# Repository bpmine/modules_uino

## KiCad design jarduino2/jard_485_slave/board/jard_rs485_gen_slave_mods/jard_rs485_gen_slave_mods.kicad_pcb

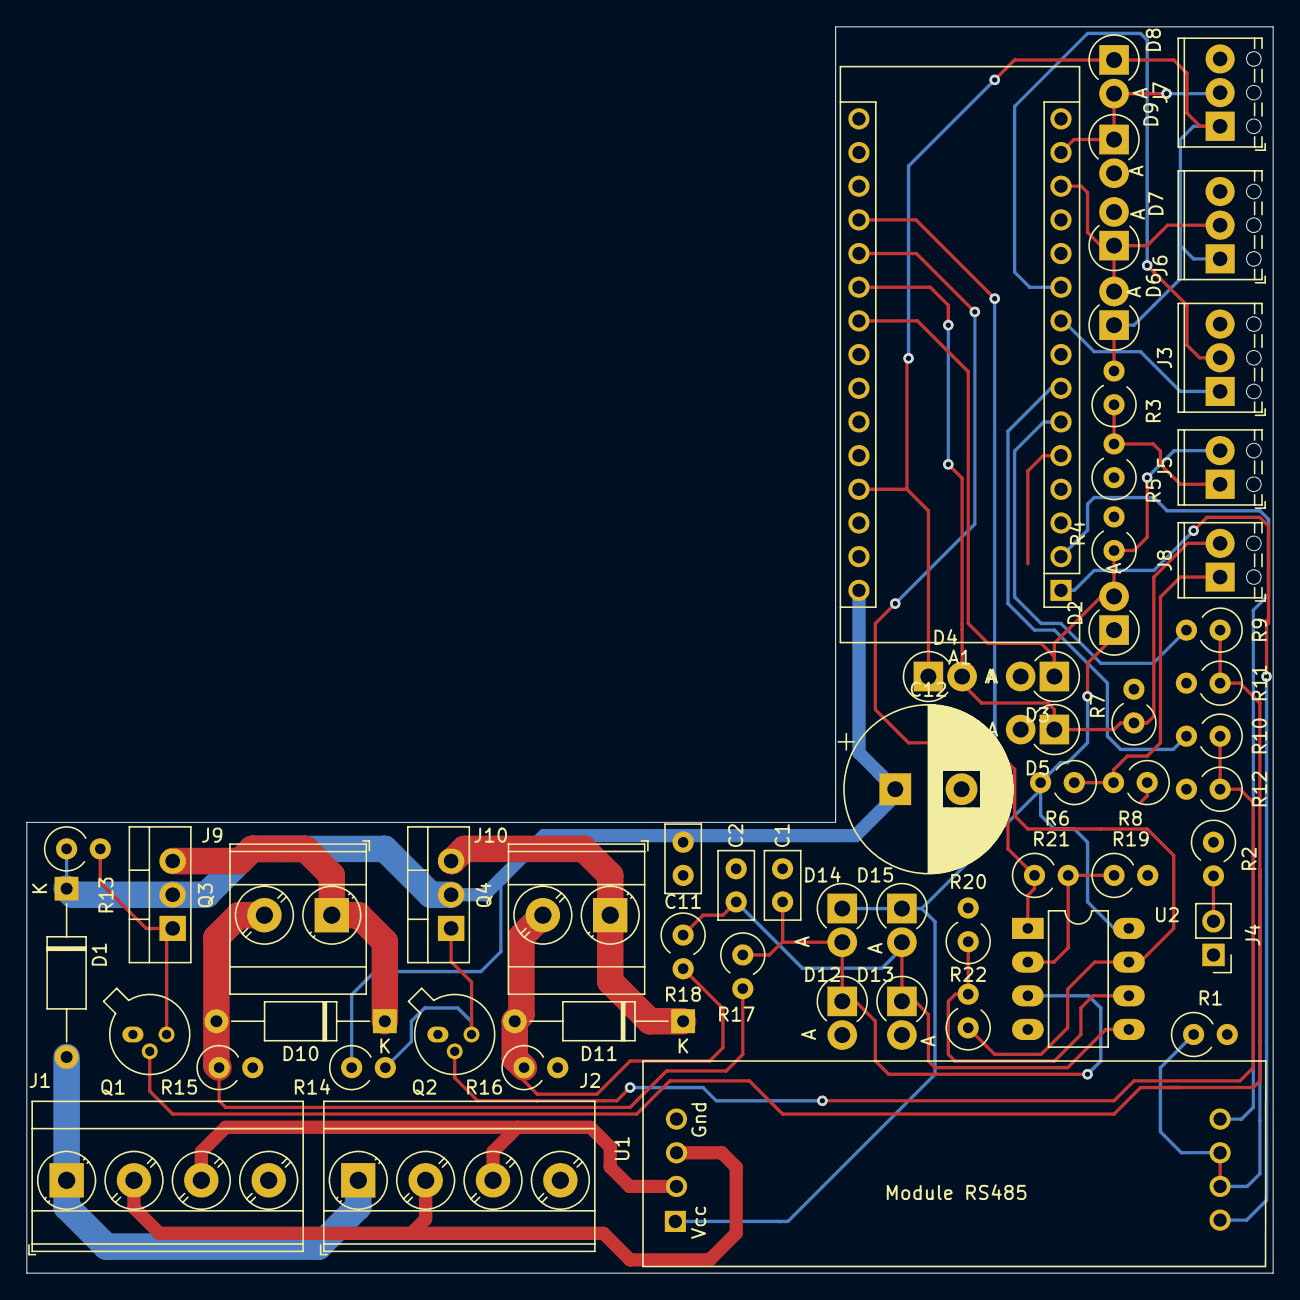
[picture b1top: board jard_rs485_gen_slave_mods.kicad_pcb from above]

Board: 2 copper layers, 94.0 x 94.0 mm, 58 parts (0 on the bottom side), 35 nets.

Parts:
A1: Arduino_Nano_v2.x; BPC_Arduino_Nano
C1, C2: C; C_Disc_D5.0mm_W2.5mm_P2.50mm
C11: 10nF; C_Disc_D5.0mm_W2.5mm_P2.50mm
C12: 20µF; CP_Radial_D12.5mm_P5.00mm
D1, D10, D11: D; D_A-405_P12.70mm_Horizontal
D2, D3, D4, D5, D6, D7, D8, D9, D12, D13, D14, D15: D_Schottky; D_DO-15_P2.54mm_Vertical_AnodeUp
J1: NETWORK IN; TerminalBlock_Phoenix_MKDS-3-4-5.08_1x04_P5.08mm_Horizontal
J2: NETWORK OUT; TerminalBlock_Phoenix_MKDS-3-4-5.08_1x04_P5.08mm_Horizontal
J3, J6, J7: Conn_01x03; TerminalBlock_Phoenix_MPT-0,5-3-2.54_1x03_P2.54mm_Horizontal
J4: LED; PinHeader_1x02_P2.54mm_Vertical
J5, J8: Conn_01x02; TerminalBlock_Phoenix_MPT-0,5-2-2.54_1x02_P2.54mm_Horizontal
J9, J10: Conn_01x02; TerminalBlock_Phoenix_MKDS-3-2-5.08_1x02_P5.08mm_Horizontal
Q1, Q2: 2N2222A; TO-18-3
Q3, Q4: bpc_mos_p03p4; TO-220-3_Vertical
R1, R11, R12, R13, R14: 100k; R_Axial_DIN0309_L9.0mm_D3.2mm_P2.54mm_Vertical
R2: 150; R_Axial_DIN0309_L9.0mm_D3.2mm_P2.54mm_Vertical
R3, R5, R6, R8: 0; R_Axial_DIN0309_L9.0mm_D3.2mm_P2.54mm_Vertical
R4, R7: 250; R_Axial_DIN0309_L9.0mm_D3.2mm_P2.54mm_Vertical
R9, R10: 50; R_Axial_DIN0309_L9.0mm_D3.2mm_P2.54mm_Vertical
R15, R16: 30m; R_Axial_DIN0309_L9.0mm_D3.2mm_P2.54mm_Vertical
R17, R18, R19, R20, R21, R22: R; R_Axial_DIN0309_L9.0mm_D3.2mm_P2.54mm_Vertical
U1: BPC_Mod485
U2: MCP6002-xP; DIP-8_W7.62mm_LongPads

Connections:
CMD_P1: A1.6, R9.2
CMD_P2: A1.7, R10.2
GND: A1.4, A1.29, C1.2, C2.2, C11.2, C12.2, D3.2, D5.2, D7.2, D9.2, D12.2, D13.2, J1.4, J2.4, J3.3, J4.1, J6.3, J7.3, Q1.1, Q2.1, R1.2, R4.2, R7.2, R11.2, R12.2, R15.2, R16.2, R19.2, R20.2, U1.4, U2.4
IN_1: A1.9, J3.1
IN_2: A1.10, J3.2
IN_PULSE_1: A1.13, D6.2, D7.1, J6.2
IN_PULSE_2: A1.14, D8.2, D9.1, J7.2
MESI_1: A1.19, R21.1, U2.1
MESI_2: A1.20, R22.1, U2.7
MESI_3: A1.21, D4.2, D5.1, J8.2, R7.1
MESI_4: A1.22, D2.2, D3.1, J5.2, R4.1
unnamed: A1.8, R2.1
unnamed: C1.1, D12.1, D14.2, R17.1, U2.3
unnamed: C2.1, D13.1, D15.2, R18.1, U2.5
unnamed: D1.2, J1.1, J2.1
unnamed: D10.1, J9.1, Q3.3
unnamed: D10.2, J9.2, R15.1, R17.2
unnamed: D11.1, J10.1, Q4.3
unnamed: D11.2, J10.2, R16.1, R18.2
unnamed: J1.2, J2.2, U1.3
unnamed: J1.3, J2.3, U1.2
unnamed: J4.2, R2.2
unnamed: J5.1, R3.1, R5.2
unnamed: J8.1, R6.1, R8.2
unnamed: Q1.2, R9.1, R11.1
unnamed: Q1.3, Q3.1, R13.2
unnamed: Q2.2, R10.1, R12.1
unnamed: Q2.3, Q4.1, R14.2
unnamed: R19.1, R21.2, U2.2
unnamed: R20.1, R22.2, U2.6
POW_MOS: A1.30, C11.1, C12.1, D1.1, Q3.2, Q4.2, R5.1, R8.1, R13.1, R14.1
RX: A1.2, U1.8
TX: A1.1, U1.5
TXEN: A1.5, R1.1, U1.6, U1.7
Vcc: A1.27, D2.1, D4.1, D6.1, D8.1, D14.1, D15.1, J6.1, J7.1, R3.2, R6.2, U1.1, U2.8

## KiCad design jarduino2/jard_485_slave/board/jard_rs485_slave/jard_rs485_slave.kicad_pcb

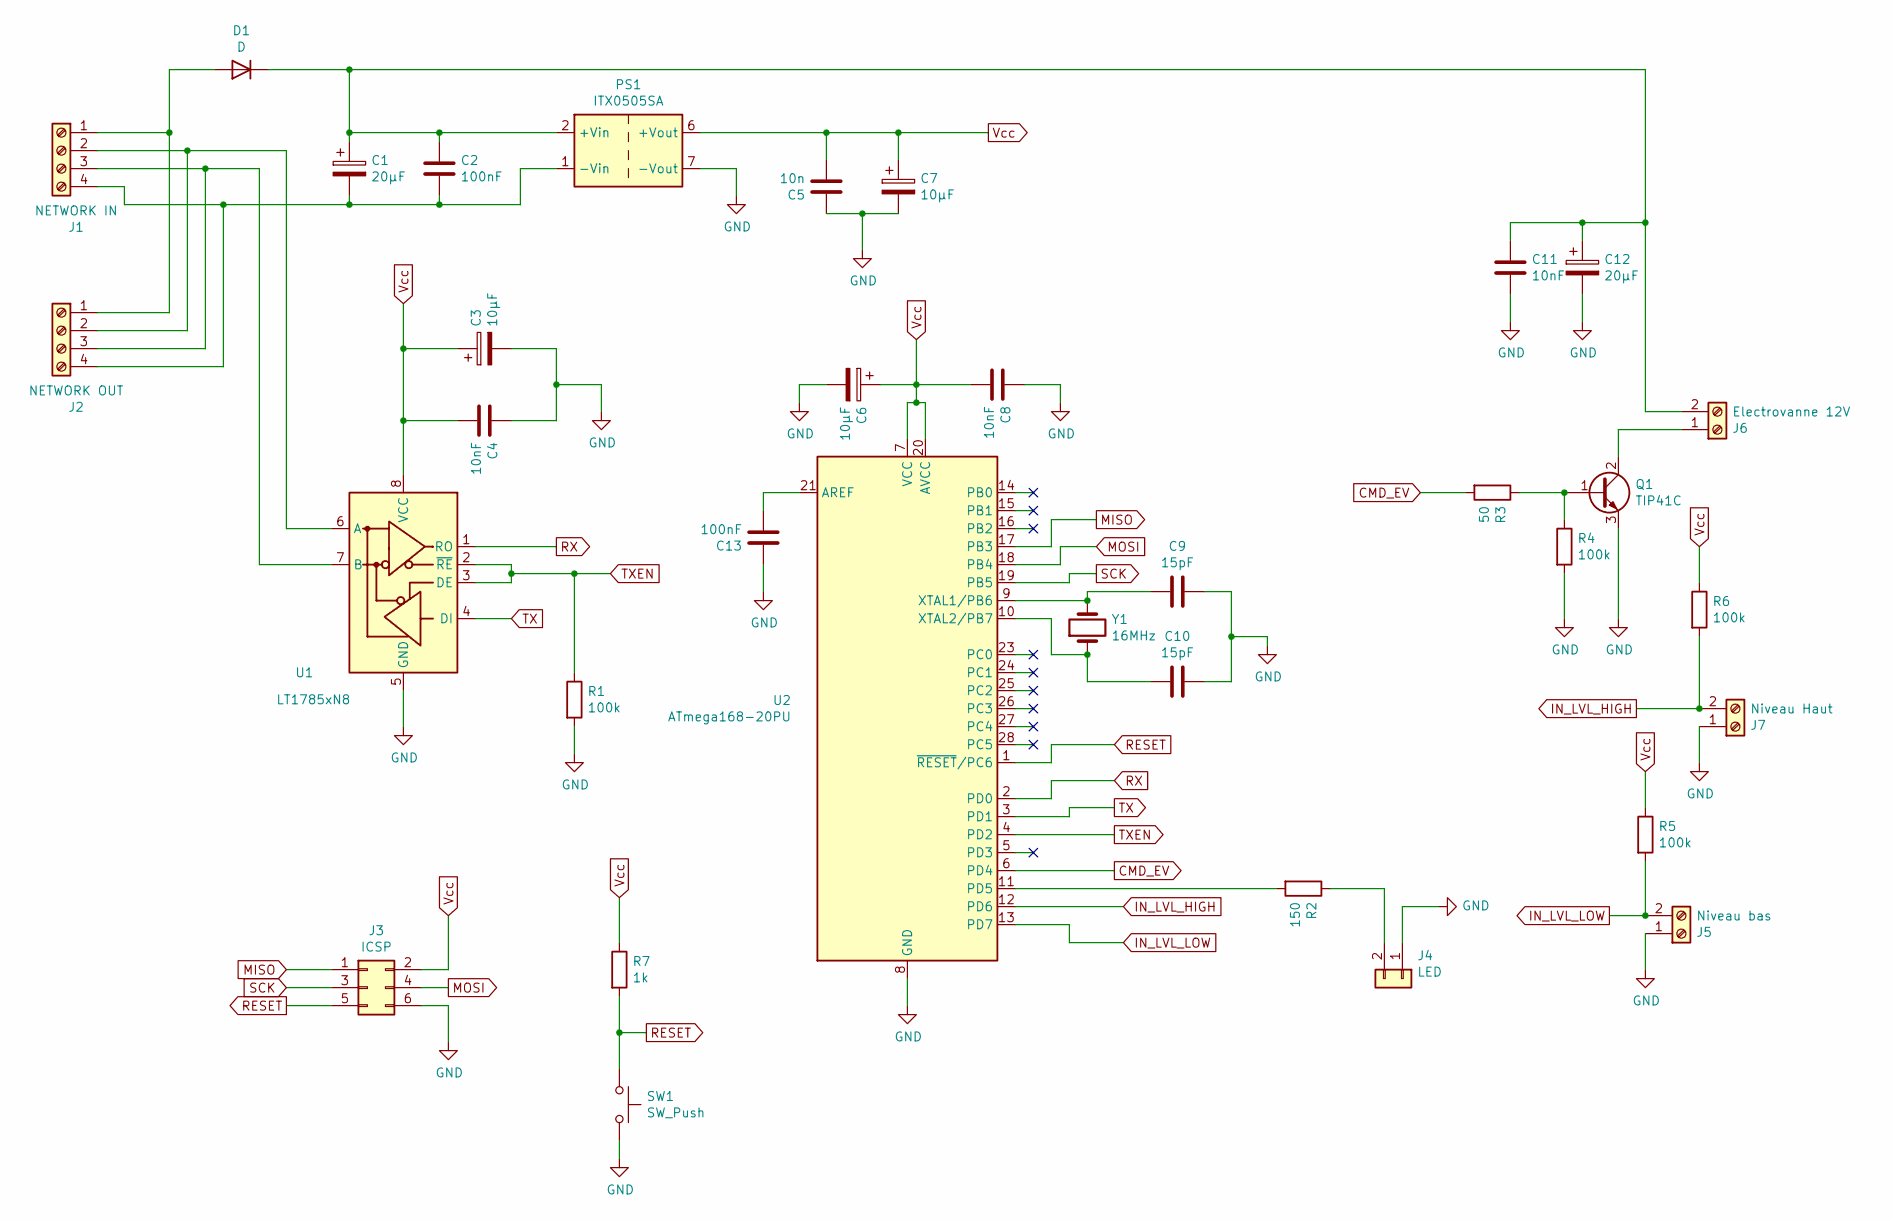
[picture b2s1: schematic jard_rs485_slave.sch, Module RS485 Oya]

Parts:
C1, C12: 20µF; CP_Radial_D12.5mm_P5.00mm
C2, C13: 100nF; C_Disc_D5.0mm_W2.5mm_P2.50mm
C3, C6, C7: 10µF; CP_Radial_D8.0mm_P2.50mm
C4, C8, C11: 10nF; C_Disc_D5.0mm_W2.5mm_P2.50mm
C5: 10n; C_Disc_D5.0mm_W2.5mm_P2.50mm
C9, C10: 15pF; C_Disc_D5.0mm_W2.5mm_P2.50mm
D1: D; D_A-405_P12.70mm_Horizontal
J1: NETWORK IN; TerminalBlock_Phoenix_MKDS-3-4-5.08_1x04_P5.08mm_Horizontal
J2: NETWORK OUT; TerminalBlock_Phoenix_MKDS-3-4-5.08_1x04_P5.08mm_Horizontal
J3: ICSP; PinHeader_2x03_P2.54mm_Vertical
J4: LED; PinHeader_1x02_P2.54mm_Vertical
J5: Niveau bas; TerminalBlock_Phoenix_MKDS-3-2-5.08_1x02_P5.08mm_Horizontal
J6: Electrovanne 12V; TerminalBlock_Phoenix_MKDS-3-2-5.08_1x02_P5.08mm_Horizontal
J7: Niveau Haut; TerminalBlock_Phoenix_MKDS-3-2-5.08_1x02_P5.08mm_Horizontal
PS1: ITX0505SA; Converter_DCDC_XP_POWER-ITXxxxxSA_THT
Q1: TIP41C; TO-220-3_Vertical
R1, R4, R5, R6: 100k; R_Axial_DIN0309_L9.0mm_D3.2mm_P2.54mm_Vertical
R2: 150; R_Axial_DIN0309_L9.0mm_D3.2mm_P2.54mm_Vertical
R3: 50; R_Axial_DIN0309_L9.0mm_D3.2mm_P2.54mm_Vertical
R7: 1k; R_Axial_DIN0309_L9.0mm_D3.2mm_P2.54mm_Vertical
SW1: SW_Push; SW_PUSH_6mm
U1: LT1785xN8; DIP-8_W7.62mm
U2: ATmega168-20PU; DIP-28_W7.62mm
Y1: 16MHz; Crystal_HC18-U_Vertical

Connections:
CMD_EV: R3.2, U2.6 (PD4)
GND: C3.2, C4.1, C5.1, C6.2, C7.2, C8.1, C9.1, C10.1, C11.2, C12.2, C13.1, J3.6, J4.1, J5.1, J7.1, PS1.7 (-Vout), Q1.3 (E), R1.2, R4.2, SW1.2, U1.5 (GND), U2.8 (GND), U2.22 (GND)
IN_LVL_HIGH: J7.2, R6.2, U2.12 (PD6)
IN_LVL_LOW: J5.2, R5.2, U2.13 (PD7)
MISO: J3.1, U2.17 (PB3)
MOSI: J3.4, U2.18 (PB4)
unnamed: C1.1, C2.1, C11.1, C12.1, D1.1 (K), J6.2, PS1.2 (+Vin)
unnamed: C1.2, C2.2, J1.4, J2.4, PS1.1 (-Vin)
unnamed: C9.2, U2.9 (XTAL1/PB6), Y1.2
unnamed: C10.2, U2.10 (XTAL2/PB7), Y1.1
unnamed: C13.2, U2.21 (AREF)
unnamed: D1.2 (A), J1.1, J2.1
unnamed: J1.2, J2.2, U1.6 (A)
unnamed: J1.3, J2.3, U1.7 (B)
unnamed: J4.2, R2.1
unnamed: J6.1, Q1.2 (C)
unnamed: Q1.1 (B), R3.1, R4.1
unnamed: R2.2, U2.11 (PD5)
RESET: J3.5, R7.2, SW1.1, U2.1 (~RESET~/PC6)
RX: U1.1 (RO), U2.2 (PD0)
SCK: J3.3, U2.19 (PB5)
TX: U1.4 (DI), U2.3 (PD1)
TXEN: R1.1, U1.2 (~RE), U1.3 (DE), U2.4 (PD2)
Vcc: C3.1, C4.2, C5.2, C6.1, C7.1, C8.2, J3.2, PS1.6 (+Vout), R5.1, R6.1, R7.1, U1.8 (VCC), U2.7 (VCC), U2.20 (AVCC)

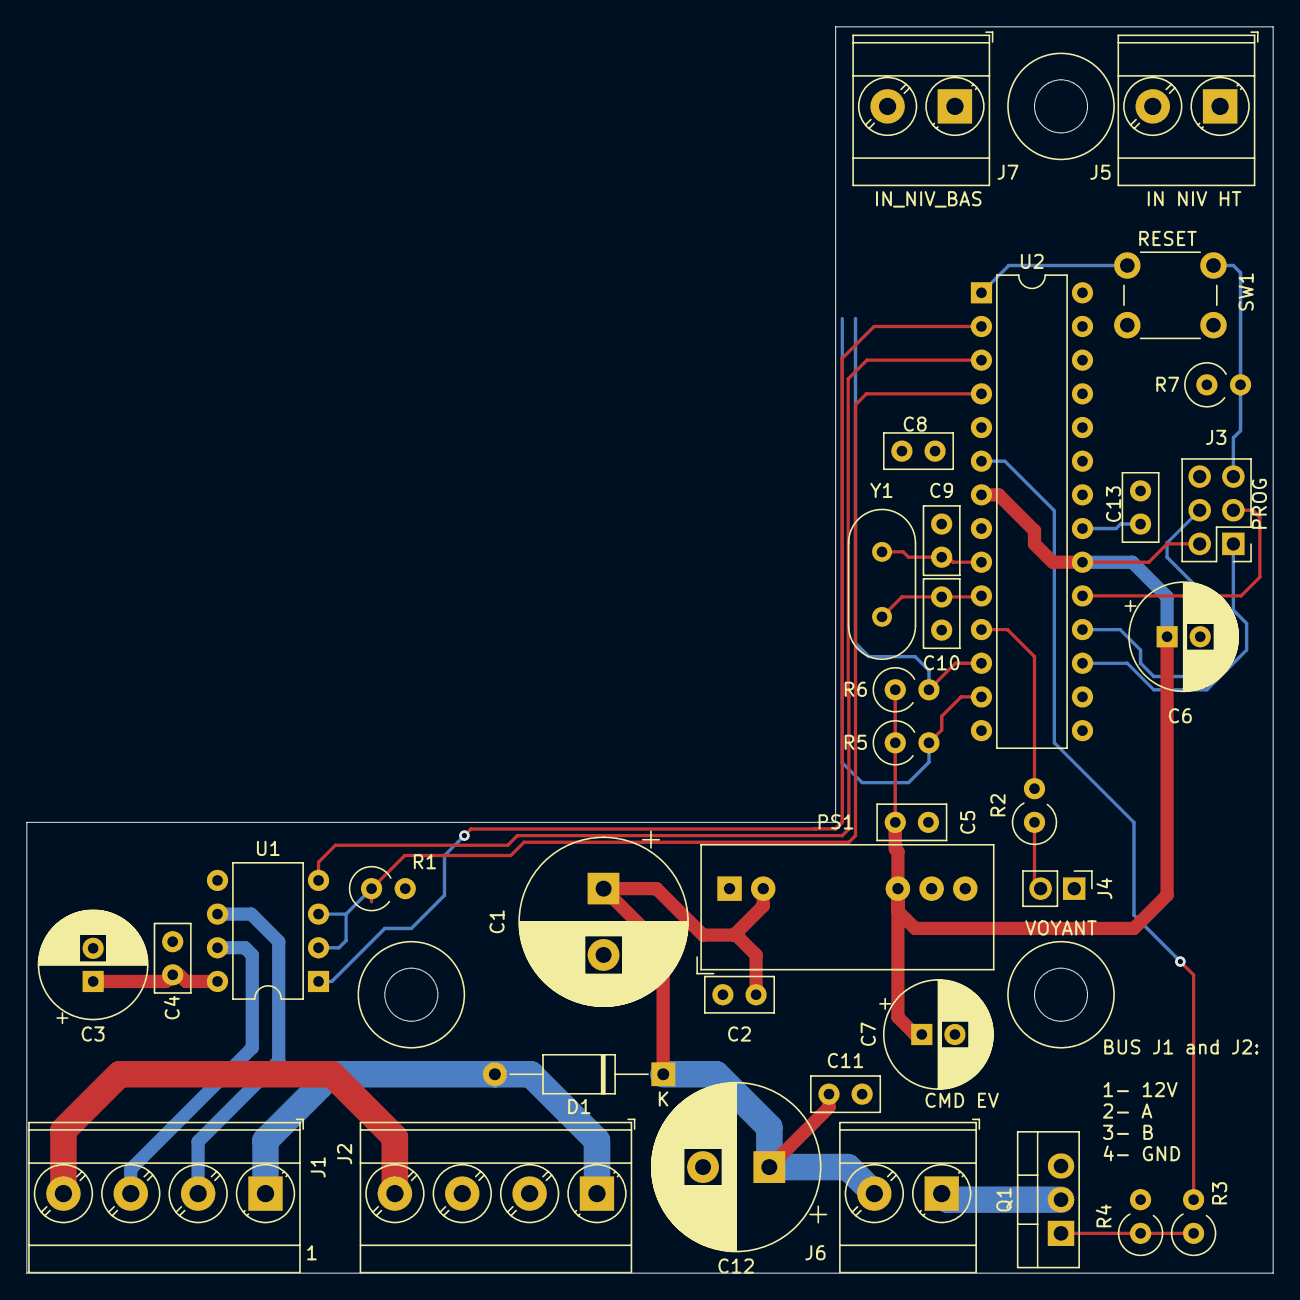
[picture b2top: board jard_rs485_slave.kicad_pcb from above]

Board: 2 copper layers, 94.0 x 94.0 mm, 34 parts (0 on the bottom side), 24 nets.

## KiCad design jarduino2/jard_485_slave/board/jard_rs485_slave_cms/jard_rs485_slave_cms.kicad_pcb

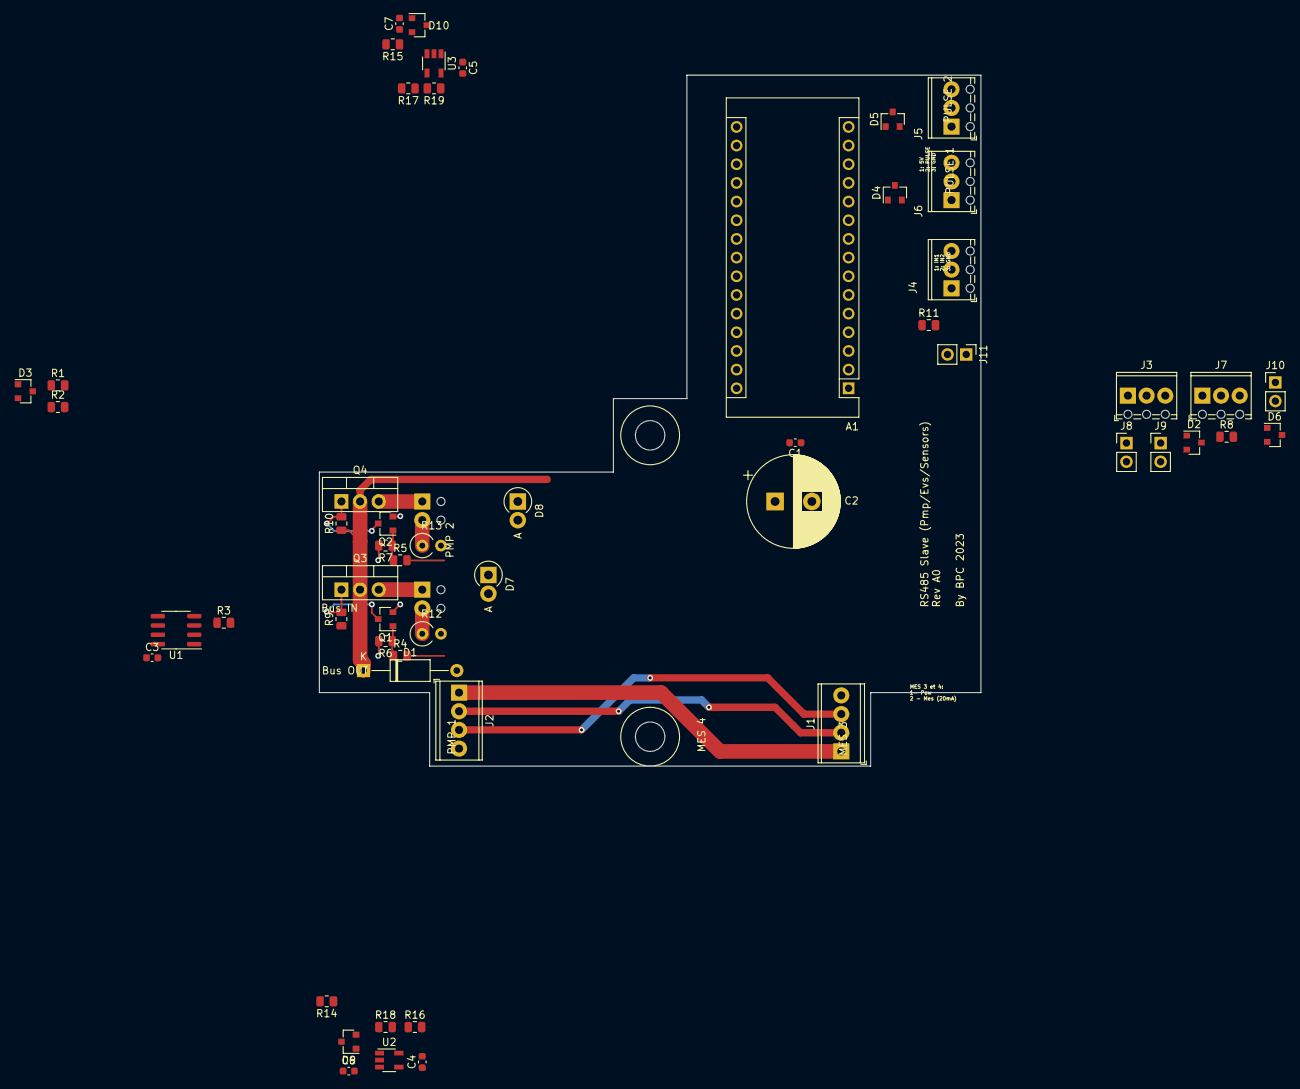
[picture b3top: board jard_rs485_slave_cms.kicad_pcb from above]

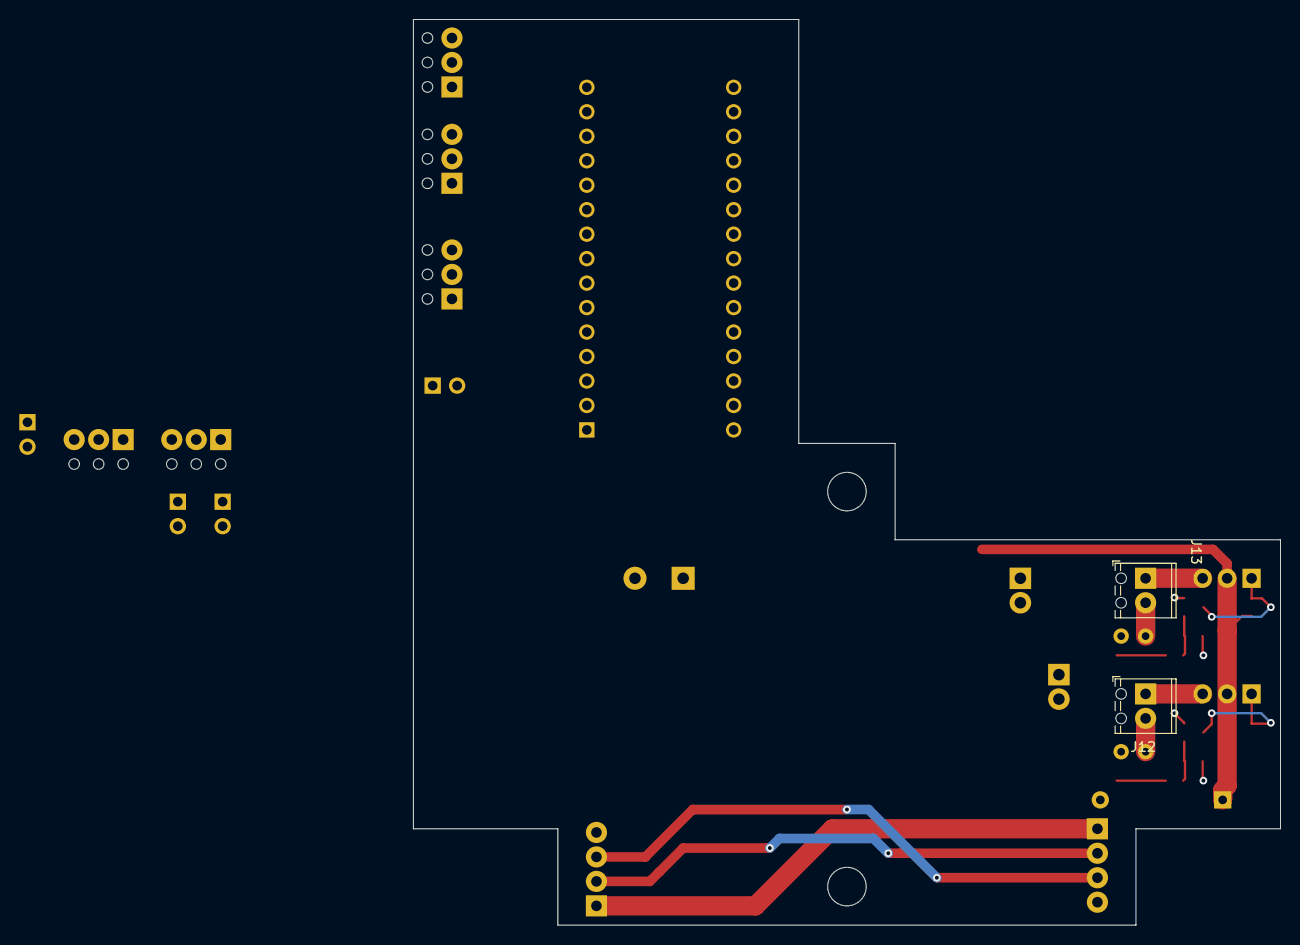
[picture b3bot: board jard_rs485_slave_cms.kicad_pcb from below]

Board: 2 copper layers, 90.0 x 94.0 mm, 57 parts (2 on the bottom side), 38 nets.

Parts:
A1: Arduino_Nano_v2.x; BPC_Arduino_Nano
C1: 10nF; C_0603_1608Metric
C2: 20µF; CP_Radial_D12.5mm_P5.00mm
C3, C4, C5: 100nF; C_0603_1608Metric
C6, C7: C; C_0603_1608Metric
D1: D; D_A-405_P12.70mm_Horizontal
D2, D3, D4, D5, D6, D9, D10: BAV99; SOT-23
D7, D8: D; D_DO-15_P2.54mm_Vertical_AnodeUp
J1: NETWORK IN; TerminalBlock_Phoenix_MPT-0,5-4-2.54_1x04_P2.54mm_Horizontal
J2: NETWORK OUT; TerminalBlock_Phoenix_MPT-0,5-4-2.54_1x04_P2.54mm_Horizontal
J3, J4, J5, J6, J7: Conn_01x03; TerminalBlock_Phoenix_MPT-0,5-3-2.54_1x03_P2.54mm_Horizontal
J8: BTN 1; PinHeader_1x02_P2.54mm_Vertical
J9: BTN 2; PinHeader_1x02_P2.54mm_Vertical
J10: LED 1; PinHeader_1x02_P2.54mm_Vertical
J11: LED 2; PinHeader_1x02_P2.54mm_Vertical
J12, J13: Conn_01x02; TerminalBlock_Phoenix_MPT-0,5-2-2.54_1x02_P2.54mm_Horizontal
Q1, Q2: MMBT5550L; SOT-23
Q3, Q4: bpc_mos_p03p4; TO-220-3_Vertical
R1, R3, R6, R7, R9, R10: 100k; R_0805_2012Metric
R2: 40k; R_0805_2012Metric
R4, R5: 50; R_0805_2012Metric
R8, R11: 150; R_0805_2012Metric
R12, R13: 30m; R_Axial_DIN0309_L9.0mm_D3.2mm_P2.54mm_Vertical
R14, R15, R16, R17, R18, R19: R; R_0805_2012Metric
U1: LT1785AxN8; SOIC-8_3.9x4.9mm_P1.27mm
U2, U3: AD8603; TSOT-23-5

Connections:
BTN1: A1.25, J8.2
BTN2: A1.26, J9.2
CMD_P1: A1.14, R4.2
CMD_P2: A1.15, R5.2
GND: A1.4, A1.29, C1.2, C2.2, C3.1, C4.1, C5.1, C6.2, C7.2, D2.1, D3.1, D4.1, D5.1, D6.1, D9.1, D10.1, J1.4, J2.4, J3.3, J4.3, J5.3, J6.3, J7.3, J8.1, J9.1, J10.1, J11.1, Q1.2, Q2.2, R2.2, R3.2, R6.2, R7.2, R12.2, R13.2, R16.2, R17.2, U1.5, U2.2, U3.2
IN_1: A1.12, J4.1
IN_2: A1.13, J4.2
IN_PULSE_1: A1.5, D2.3, J3.2
IN_PULSE_2: A1.6, D6.3, J7.2
IN_PULSE_3: A1.7, D4.3, J6.2
IN_PULSE_4: A1.8, D5.3, J5.2
LED1: A1.10, R8.1
LED2: A1.11, R11.1
MESI_1: A1.19, R18.1, U2.1
MESI_2: A1.20, R19.1, U3.1
MES_POW: A1.24, D3.3, R1.2, R2.1
unnamed: C6.1, D9.3, R14.1, U2.3
unnamed: C7.1, D10.3, R15.1, U3.3
unnamed: D1.2, J1.1, J2.1
unnamed: D7.1, J12.1, Q3.3
unnamed: D7.2, J12.2, R12.1, R14.2
unnamed: D8.1, J13.1, Q4.3
unnamed: D8.2, J13.2, R13.1, R15.2
unnamed: J1.2, J2.2, U1.7
unnamed: J1.3, J2.3, U1.6
unnamed: J10.2, R8.2
unnamed: J11.2, R11.2
unnamed: Q1.1, R4.1, R6.1
unnamed: Q1.3, Q3.1, R9.2
unnamed: Q2.1, R5.1, R7.1
unnamed: Q2.3, Q4.1, R10.2
unnamed: R16.1, R18.2, U2.4
unnamed: R17.1, R19.2, U3.4
POW_MOS: A1.30, C1.1, C2.1, D1.1, Q3.2, Q4.2, R1.1, R9.1, R10.1
RX: A1.2, U1.1
TX: A1.1, U1.4
TXEN: A1.9, R3.1, U1.2, U1.3
Vcc: A1.27, C3.2, C4.2, C5.2, D2.2, D3.2, D4.2, D5.2, D6.2, D9.2, D10.2, J3.1, J5.1, J6.1, J7.1, U1.8, U2.5, U3.5

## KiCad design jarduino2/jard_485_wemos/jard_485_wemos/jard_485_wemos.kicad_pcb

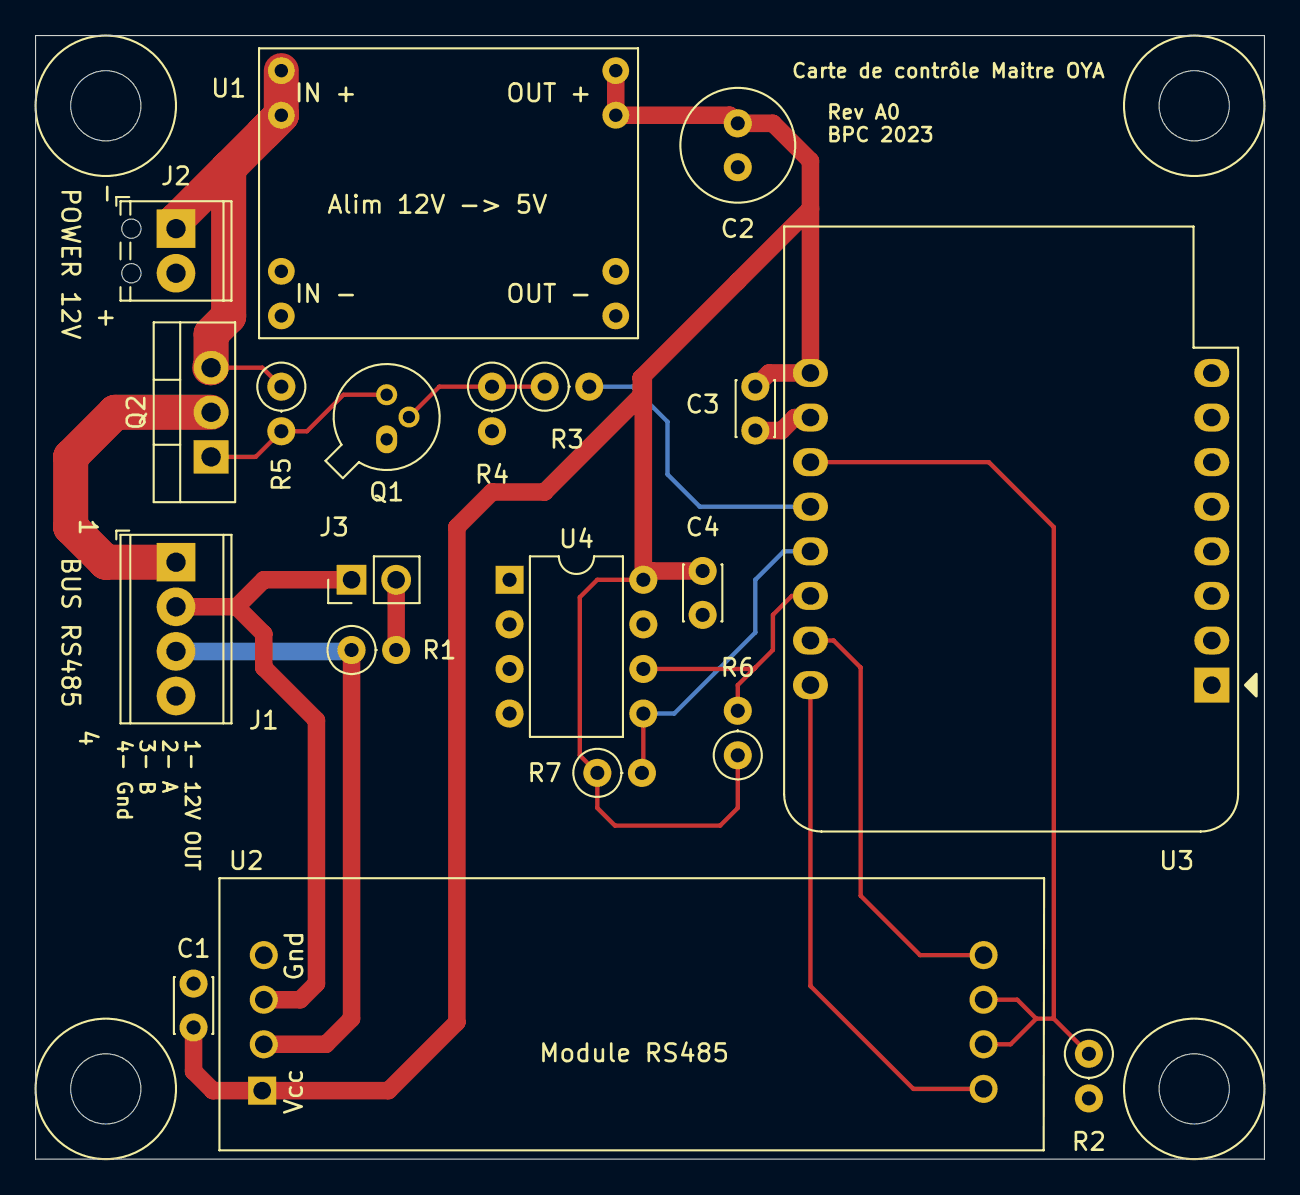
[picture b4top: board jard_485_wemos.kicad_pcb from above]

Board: 2 copper layers, 70.0 x 64.0 mm, 20 parts (0 on the bottom side), 15 nets.

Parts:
C1, C3, C4: 100n; C_Disc_D3.0mm_W2.0mm_P2.50mm
C2: CP; C_Radial_D6.3mm_H7.0mm_P2.50mm
J1: Conn_01x04; TerminalBlock_Phoenix_MPT-0,5-4-2.54_1x04_P2.54mm_Horizontal
J2: Conn_01x02; TerminalBlock_Phoenix_MPT-0,5-2-2.54_1x02_P2.54mm_Horizontal
J3: Conn_01x02; PinHeader_1x02_P2.54mm_Vertical
Q1: BPC_2N2222A; TO-18-3
Q2: P03P4L-04; TO-220-3_Vertical
R1: 128; R_Axial_DIN0207_L6.3mm_D2.5mm_P2.54mm_Vertical
R2, R4, R5: 100k; R_Axial_DIN0207_L6.3mm_D2.5mm_P2.54mm_Vertical
R3: 50; R_Axial_DIN0207_L6.3mm_D2.5mm_P2.54mm_Vertical
R6, R7: 10k; R_Axial_DIN0207_L6.3mm_D2.5mm_P2.54mm_Vertical
U1: BPC_Alim5V
U2: BPC_Mod485
U3: WeMos_D1_mini; WEMOS_D1_mini_light
U4: 24LC01; DIP-8_W7.62mm

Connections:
+5V: C1.2, C2.1, C3.1, C4.2, R6.1, R7.1, U1.7, U1.8, U2.1, U3.9, U4.8
+12V: J2.1, Q2.3, R5.1, U1.1, U1.2
CMD_OUT_12V: R3.2, U3.12
GND: C1.1, C2.2, C3.2, C4.1, J1.4, J2.2, Q1.1, R2.2, R4.2, U1.3, U1.4, U1.5, U1.6, U2.4, U3.10, U4.4, U4.7
unnamed: J1.2, J3.1, U2.3
unnamed: J1.3, R1.1, U2.2
unnamed: J3.2, R1.2
unnamed: Q1.2, R3.1, R4.1
unnamed: Q1.3, Q2.1, R5.2
unnamed: R6.2, U3.14, U4.6
unnamed: R7.2, U3.13, U4.5
OUT_12V: J1.1, Q2.2
UC_RX: U2.5, U3.15
UC_TX: U2.8, U3.16
UC_TXEN: R2.1, U2.6, U2.7, U3.11

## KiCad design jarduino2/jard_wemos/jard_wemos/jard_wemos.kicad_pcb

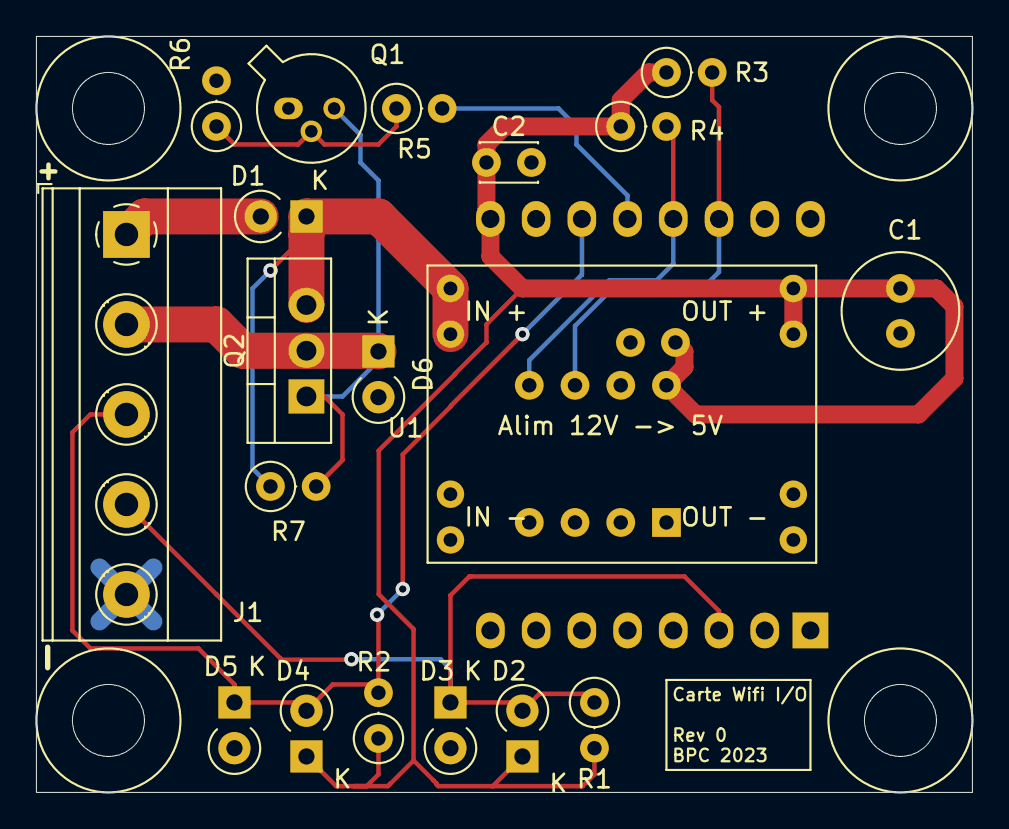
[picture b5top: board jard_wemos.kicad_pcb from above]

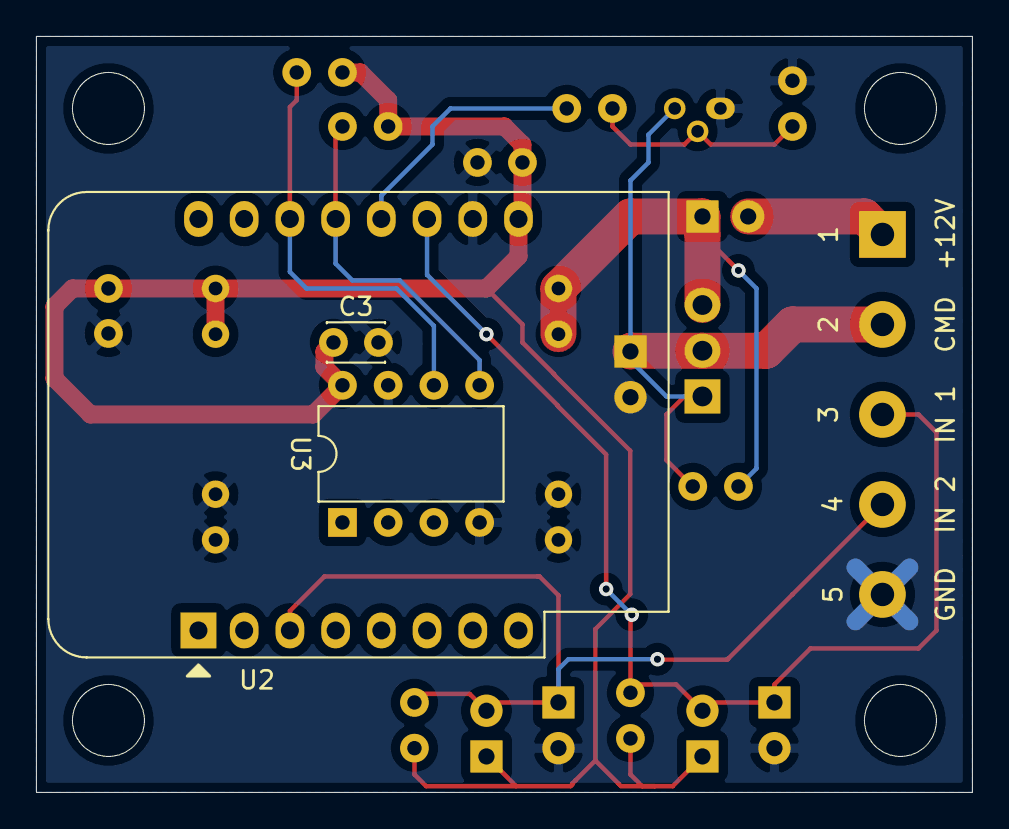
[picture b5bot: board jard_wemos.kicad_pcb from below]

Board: 2 copper layers, 52.0 x 42.0 mm, 22 parts (3 on the bottom side), 12 nets.

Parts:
C1: 20µF; C_Radial_D6.3mm_H7.0mm_P2.50mm
C2, C3: 100n; C_Disc_D3.0mm_W2.0mm_P2.50mm
D1, D2, D3, D4, D5, D6: D; D_A-405_P2.54mm_Vertical_KathodeUp
J1: Conn_01x05; TerminalBlock_Phoenix_MKDS-1,5-5_1x05_P5.00mm_Horizontal
Q1: BPC_2N2222A; TO-18-3
Q2: P03P4L-04; TO-220-3_Vertical
R1, R2, R6, R7: 100k; R_Axial_DIN0207_L6.3mm_D2.5mm_P2.54mm_Vertical
R3, R4: 10k; R_Axial_DIN0207_L6.3mm_D2.5mm_P2.54mm_Vertical
R5: 50; R_Axial_DIN0207_L6.3mm_D2.5mm_P2.54mm_Vertical
U1: BPC_Alim5V
U2: WeMos_D1_mini; WEMOS_D1_mini_light
U3: 24LC01; DIP-8_W7.62mm

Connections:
+5V: C1.1, C2.1, C3.2, D2.1, D4.1, R1.2, R2.1, R3.1, R4.1, U1.7, U1.8, U2.9, U3.8
+12V: D1.1, Q2.3, R7.1, U1.1, U1.2
CMD_OUT_12V: R5.2, U2.12
GND: C1.2, C2.2, C3.1, D3.2, D5.2, D6.2, J1.5, Q1.1, R6.2, U1.3, U1.4, U1.5, U1.6, U2.10, U3.4, U3.7
IN_1: D4.2, D5.1, J1.3, R2.2, U2.11
IN_2: D2.2, D3.1, J1.4, R1.1, U2.3
unnamed: D1.2, J1.1
unnamed: Q1.2, R5.1, R6.1
unnamed: Q1.3, Q2.1, R7.2
unnamed: R3.2, U2.14, U3.6
unnamed: R4.2, U2.13, U3.5
OUT_12V: D6.1, J1.2, Q2.2

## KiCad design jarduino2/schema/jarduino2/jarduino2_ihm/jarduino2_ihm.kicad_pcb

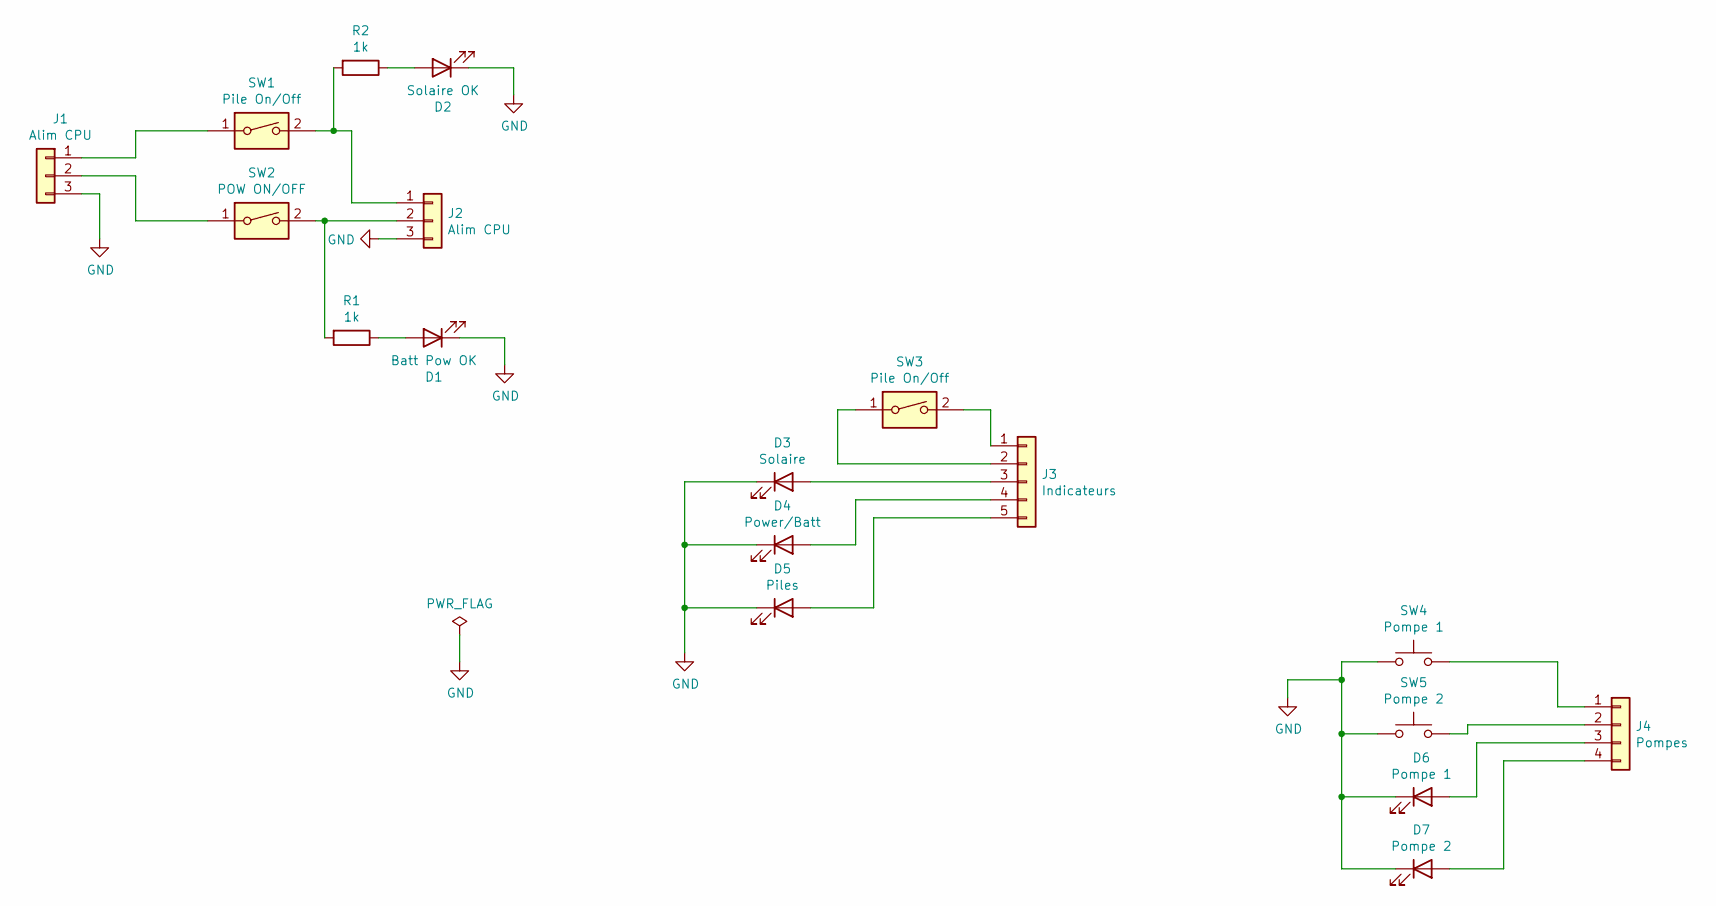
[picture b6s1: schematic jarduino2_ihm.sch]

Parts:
D1: Batt Pow OK; LED_D3.0mm_Clear
D2: Solaire OK; LED_D3.0mm_Clear
D3: Solaire; LED_D3.0mm_Clear
D4: Power/Batt; LED_D3.0mm_Clear
D5: Piles; LED_D3.0mm_Clear
D6: Pompe 1; LED_D3.0mm_Clear
D7: Pompe 2; LED_D3.0mm_Clear
J1, J2: Alim CPU; PinHeader_1x03_P2.54mm_Vertical
J3: Indicateurs; PinHeader_1x05_P2.54mm_Vertical
J4: Pompes; PinHeader_1x04_P2.54mm_Vertical
R1, R2: 1k; R_Axial_DIN0309_L9.0mm_D3.2mm_P20.32mm_Horizontal
SW1, SW3: Pile On/Off; PinHeader_1x02_P2.54mm_Vertical
SW2: POW ON/OFF; PinHeader_1x02_P2.54mm_Vertical
SW4: Pompe 1; PinHeader_1x02_P2.54mm_Vertical
SW5: Pompe 2; PinHeader_1x02_P2.54mm_Vertical

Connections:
GND: D1.1 (K), D2.1 (K), D3.1 (K), D4.1 (K), D5.1 (K), D6.1 (K), D7.1 (K), J1.3, J2.3, SW4.1, SW5.1
unnamed: D1.2 (A), R1.1
unnamed: D2.2 (A), R2.1
unnamed: D3.2 (A), J3.3
unnamed: D4.2 (A), J3.4
unnamed: D5.2 (A), J3.5
unnamed: D6.2 (A), J4.3
unnamed: D7.2 (A), J4.4
unnamed: J1.1, SW1.1
unnamed: J1.2, SW2.1
unnamed: J2.1, R2.2, SW1.2
unnamed: J2.2, R1.2, SW2.2
unnamed: J3.1, SW3.2
unnamed: J3.2, SW3.1
unnamed: J4.1, SW4.2
unnamed: J4.2, SW5.2

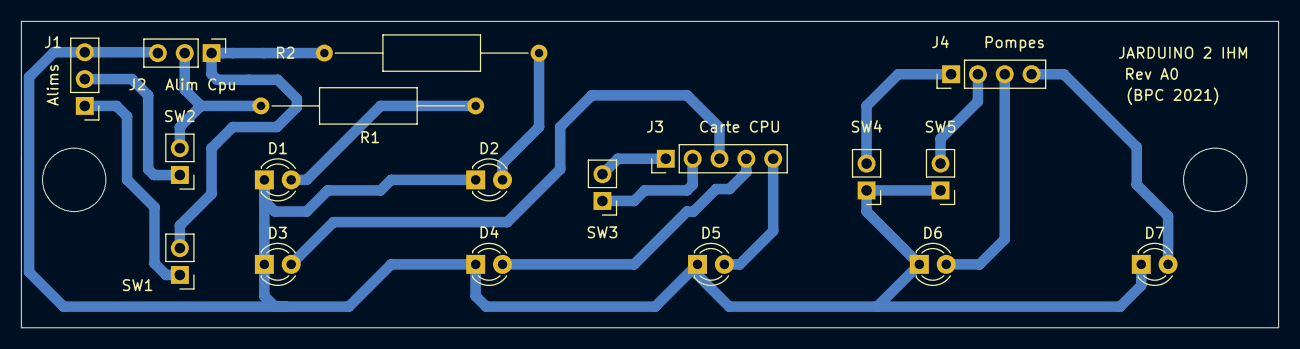
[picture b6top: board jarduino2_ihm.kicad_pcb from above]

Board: 2 copper layers, 119.0 x 29.0 mm, 18 parts (0 on the bottom side), 16 nets.
